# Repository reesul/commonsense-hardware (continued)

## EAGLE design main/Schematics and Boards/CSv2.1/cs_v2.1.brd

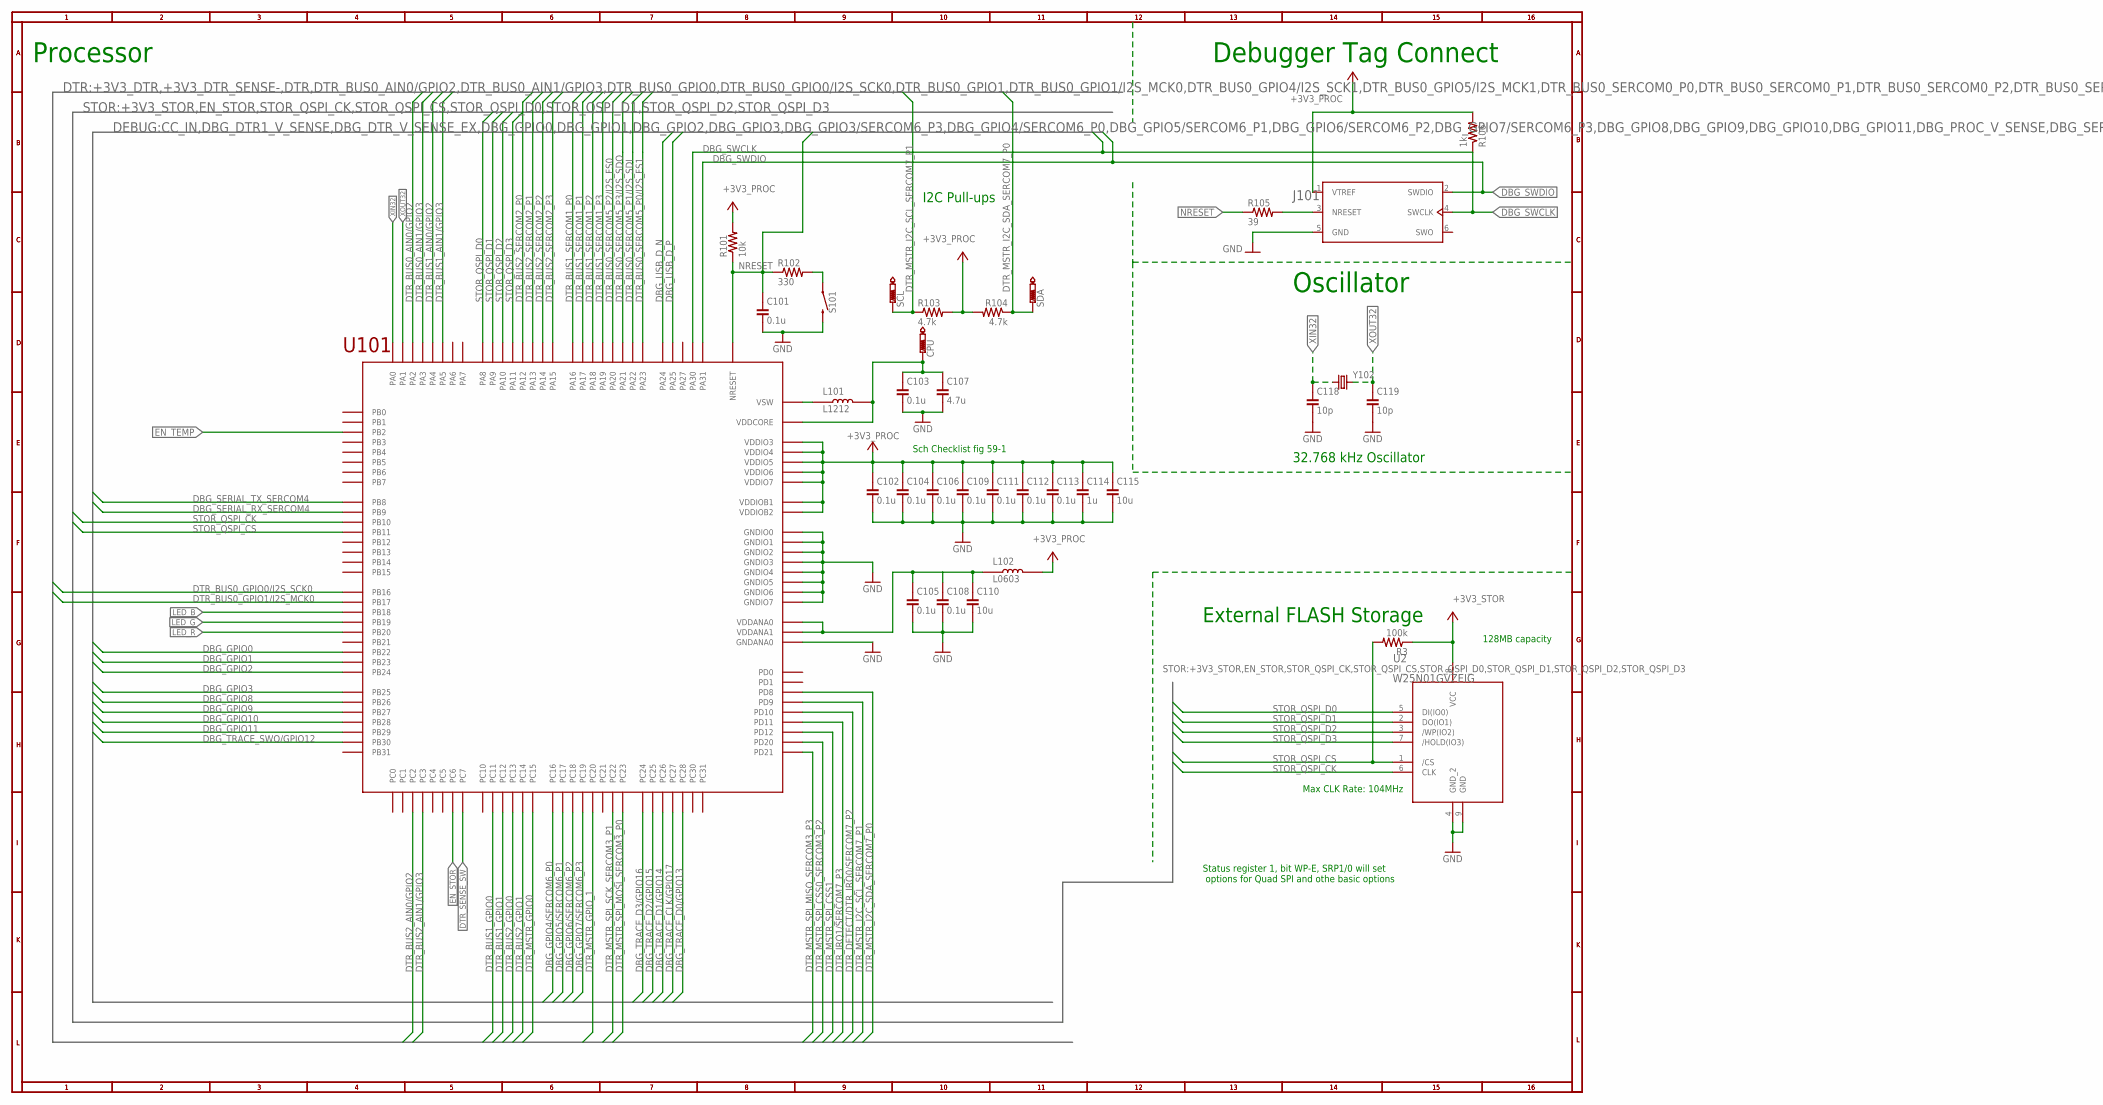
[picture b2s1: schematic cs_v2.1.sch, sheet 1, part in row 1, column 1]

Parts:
C101, C102, C103, C104, C105, C106, C108, C109, C111, C112, C113: 0.1u; C0402; VOLTAGE 10V; PART_NO C0402C104K8RACTU
C107: 4.7u; C0805; VOLTAGE 10V; PART_NO C0805C475K8RACTU
C110, C115: 10u; C0805; VOLTAGE 10V; PART_NO C0805C106M8RACTU
C114: 1u; C0402; VOLTAGE 10V; MPN C0402C105M8PACTU
C118, C119: 10p; C0402; PART_NO C0402C100C8GACTU
CPU: PTR1TP10SQ; TP10SQ
J101: J-JTAG-CORTEX-NEEDLE6-LEGS; 8.06.16_6-PIN_NEEDLE_ADAPTER_LEGS
L101: L1212; PART_NO LQH3NPN100MMEL
L102: L0603; PART_NO BLM18PG471SN1D
R3: 100k; R0402; MPN ERJ-2GEJ104X
R101: 10k; R0402; MPN ERJ-2GEJ103X
R102: 330; R0402; PART_NO ERJ-2GEJ331X
R103, R104: 4.7k; R0402; PART_NO ERJ-2GEJ472X
R105: 39; R0402; PART_NO ERJ-2GEJ390X
R106: 1k; R0402; PART_NO ERJ-2GEJ102X
S101: SW_EVQ-P7L01P_SPST_RA; SW_EVQ-P7L01P
SCL: PTR1TP10SQ; TP10SQ
SDA: PTR1TP10SQ; TP10SQ
U2: W25N01GVZEIG; WSON-8_W15N; MANUFACTURER_PART_NUMBER W25N01GVZEIG TR
U101: ATSAMD51; TFBGA120
Y102: ABS07-32.768KHZ-9-T; XTAL320X150X90

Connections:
+3V3_PROC: C102.1, C104.1, C106.1, C109.1, C111.1, C112.1, C113.1, C114.1, C115.1, J101.1 (VTREF), L102.2, R101.2, R103.2, R104.2, R106.2, U101.VDDIO3, U101.VDDIO4, U101.VDDIO5, U101.VDDIO6, U101.VDDIO7, U101.VDDIOB1, U101.VDDIOB2; also elsewhere on the board
+3V3_STOR: R3.1, U2.8 (VCC); also elsewhere on the board
DBG_GPIO0: U101.PB22; also elsewhere on the board
DBG_GPIO1: U101.PB23; also elsewhere on the board
DBG_GPIO2: U101.PB24; also elsewhere on the board
DBG_GPIO3: U101.PB25; also elsewhere on the board
DBG_GPIO4/SERCOM6_P0: U101.PC16; also elsewhere on the board
DBG_GPIO5/SERCOM6_P1: U101.PC17; also elsewhere on the board
DBG_GPIO6/SERCOM6_P2: U101.PC18; also elsewhere on the board
DBG_GPIO7/SERCOM6_P3: U101.PC19; also elsewhere on the board
DBG_GPIO8: U101.PB26; also elsewhere on the board
DBG_GPIO9: U101.PB27; also elsewhere on the board
DBG_GPIO10: U101.PB28; also elsewhere on the board
DBG_GPIO11: U101.PB29; also elsewhere on the board
DBG_SERIAL_RX_SERCOM4: U101.PB09 (PB9); also elsewhere on the board
DBG_SERIAL_TX_SERCOM4: U101.PB08 (PB8); also elsewhere on the board
DBG_SWCLK: J101.4 (SWCLK), R106.1, U101.PA30; also elsewhere on the board
DBG_SWDIO: J101.2 (SWDIO), U101.PA31; also elsewhere on the board
DBG_TRACE_CLK/GPIO17: U101.PC27; also elsewhere on the board
DBG_TRACE_D0/GPIO13: U101.PC28; also elsewhere on the board
DBG_TRACE_D1/GPIO14: U101.PC26; also elsewhere on the board
DBG_TRACE_D2/GPIO15: U101.PC25; also elsewhere on the board
DBG_TRACE_D3/GPIO16: U101.PC24; also elsewhere on the board
DBG_TRACE_SWO/GPIO12: U101.PB30; also elsewhere on the board
DBG_USB_D_N: U101.PA24; also elsewhere on the board
DBG_USB_D_P: U101.PA25; also elsewhere on the board
DTR_BUS0_AIN0/GPIO2: U101.PA02 (PA2); also elsewhere on the board
DTR_BUS0_AIN1/GPIO3: U101.PA03 (PA3); also elsewhere on the board
DTR_BUS0_GPIO0/I2S_SCK0: U101.PB16; also elsewhere on the board
DTR_BUS0_GPIO1/I2S_MCK0: U101.PB17; also elsewhere on the board
DTR_BUS0_SERCOM5_P0/I2S_FS1: U101.PA23; also elsewhere on the board
DTR_BUS0_SERCOM5_P1/I2S_SDI: U101.PA22; also elsewhere on the board
DTR_BUS0_SERCOM5_P2/I2S_FS0: U101.PA20; also elsewhere on the board
DTR_BUS0_SERCOM5_P3/I2S_SDO: U101.PA21; also elsewhere on the board
DTR_BUS1_AIN0/GPIO2: U101.PA04 (PA4); also elsewhere on the board
DTR_BUS1_AIN1/GPIO3: U101.PA05 (PA5); also elsewhere on the board
DTR_BUS1_GPIO0: U101.PC11; also elsewhere on the board
DTR_BUS1_GPIO1: U101.PC12; also elsewhere on the board
DTR_BUS1_SERCOM1_P0: U101.PA16; also elsewhere on the board
DTR_BUS1_SERCOM1_P1: U101.PA17; also elsewhere on the board
DTR_BUS1_SERCOM1_P2: U101.PA18; also elsewhere on the board
DTR_BUS1_SERCOM1_P3: U101.PA19; also elsewhere on the board
DTR_BUS2_AIN0/GPIO2: U101.PC02 (PC2); also elsewhere on the board
DTR_BUS2_AIN1/GPIO3: U101.PC03 (PC3); also elsewhere on the board
DTR_BUS2_GPIO0: U101.PC13; also elsewhere on the board
DTR_BUS2_GPIO1: U101.PC14; also elsewhere on the board
DTR_BUS2_SERCOM2_P0: U101.PA12; also elsewhere on the board
DTR_BUS2_SERCOM2_P1: U101.PA13; also elsewhere on the board
DTR_BUS2_SERCOM2_P2: U101.PA14; also elsewhere on the board
DTR_BUS2_SERCOM2_P3: U101.PA15; also elsewhere on the board
DTR_DETECT/DTR_IRQ0/SERCOM7_P2: U101.PD10; also elsewhere on the board
DTR_IRQ1/SERCOM7_P3: U101.PD11; also elsewhere on the board
DTR_MSTR_GPIO0: U101.PC15; also elsewhere on the board
DTR_MSTR_GPIO_1: U101.PC20
DTR_MSTR_I2C_SCL_SERCOM7_P1: R103.1, SCL.TP, U101.PD09 (PD9); also elsewhere on the board
DTR_MSTR_I2C_SDA_SERCOM7_P0: R104.1, SDA.TP, U101.PD08 (PD8); also elsewhere on the board
DTR_MSTR_SPI_CSS0_SERCOM3_P2: U101.PD20; also elsewhere on the board
DTR_MSTR_SPI_CSS1: U101.PD12; also elsewhere on the board
DTR_MSTR_SPI_MISO_SERCOM3_P3: U101.PD21; also elsewhere on the board
DTR_MSTR_SPI_MOSI_SERCOM3_P0: U101.PC23; also elsewhere on the board
DTR_MSTR_SPI_SCK_SERCOM3_P1: U101.PC22; also elsewhere on the board
DTR_SENSE_SW: U101.PC07 (PC7); also elsewhere on the board
EN_STOR: U101.PC06 (PC6); also elsewhere on the board
EN_TEMP: U101.PB02 (PB2); also elsewhere on the board
GND: C101.2, C102.2, C103.2, C104.2, C105.2, C106.2, C107.2, C108.2, C109.2, C110.2, C111.2, C112.2, C113.2, C114.2, C115.2, C118.2, C119.2, J101.5 (GND), S101.2_1 (2), S101.2_2 (2), U2.4 (GND_2), U2.9 (GND), U101.GNDANA0, U101.GNDIO0, U101.GNDIO1, U101.GNDIO2, U101.GNDIO3, U101.GNDIO4, U101.GNDIO5, U101.GNDIO6, U101.GNDIO7; also elsewhere on the board
JTAG_NRESET: J101.3 (NRESET), R105.2
LED_B: U101.PB18; also elsewhere on the board
LED_G: U101.PB19; also elsewhere on the board
LED_R: U101.PB20; also elsewhere on the board
unnamed: R102.2, S101.1_1 (1), S101.1_2 (1)
NRESET: C101.1, R101.1, R102.1, R105.1, U101.NRESET; also elsewhere on the board
STOR_QSPI_CK: U2.6 (CLK), U101.PB10
STOR_QSPI_CS: R3.2, U2.1 (/CS), U101.PB11
STOR_QSPI_D0: U2.5 (DI(IO0)), U101.PA08 (PA8)
STOR_QSPI_D1: U2.2 (DO(IO1)), U101.PA09 (PA9)
STOR_QSPI_D2: U2.3 (/WP(IO2)), U101.PA10
STOR_QSPI_D3: U2.7 (/HOLD(IO3)), U101.PA11
VDDANA: C105.1, C108.1, C110.1, L102.1, U101.VDDANA0, U101.VDDANA1
VDDCORE: C103.1, C107.1, CPU.TP, L101.P$2 (2), U101.VDDCORE
VSW: L101.P$1 (1), U101.VSW
XIN32: C118.1, U101.PA00 (PA0), Y102.1
XOUT32: C119.1, U101.PA01 (PA1), Y102.2

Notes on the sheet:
Sch Checklist fig 59-1
Oscillator
32.768 kHz Oscillator
Processor
Debugger Tag Connect
I2C Pull-ups
External FLASH Storage
128MB capacity
Max CLK Rate: 104MHz
Status register 1, bit WP-E, SRP1/0 will set options for Quad SPI and othe basic options

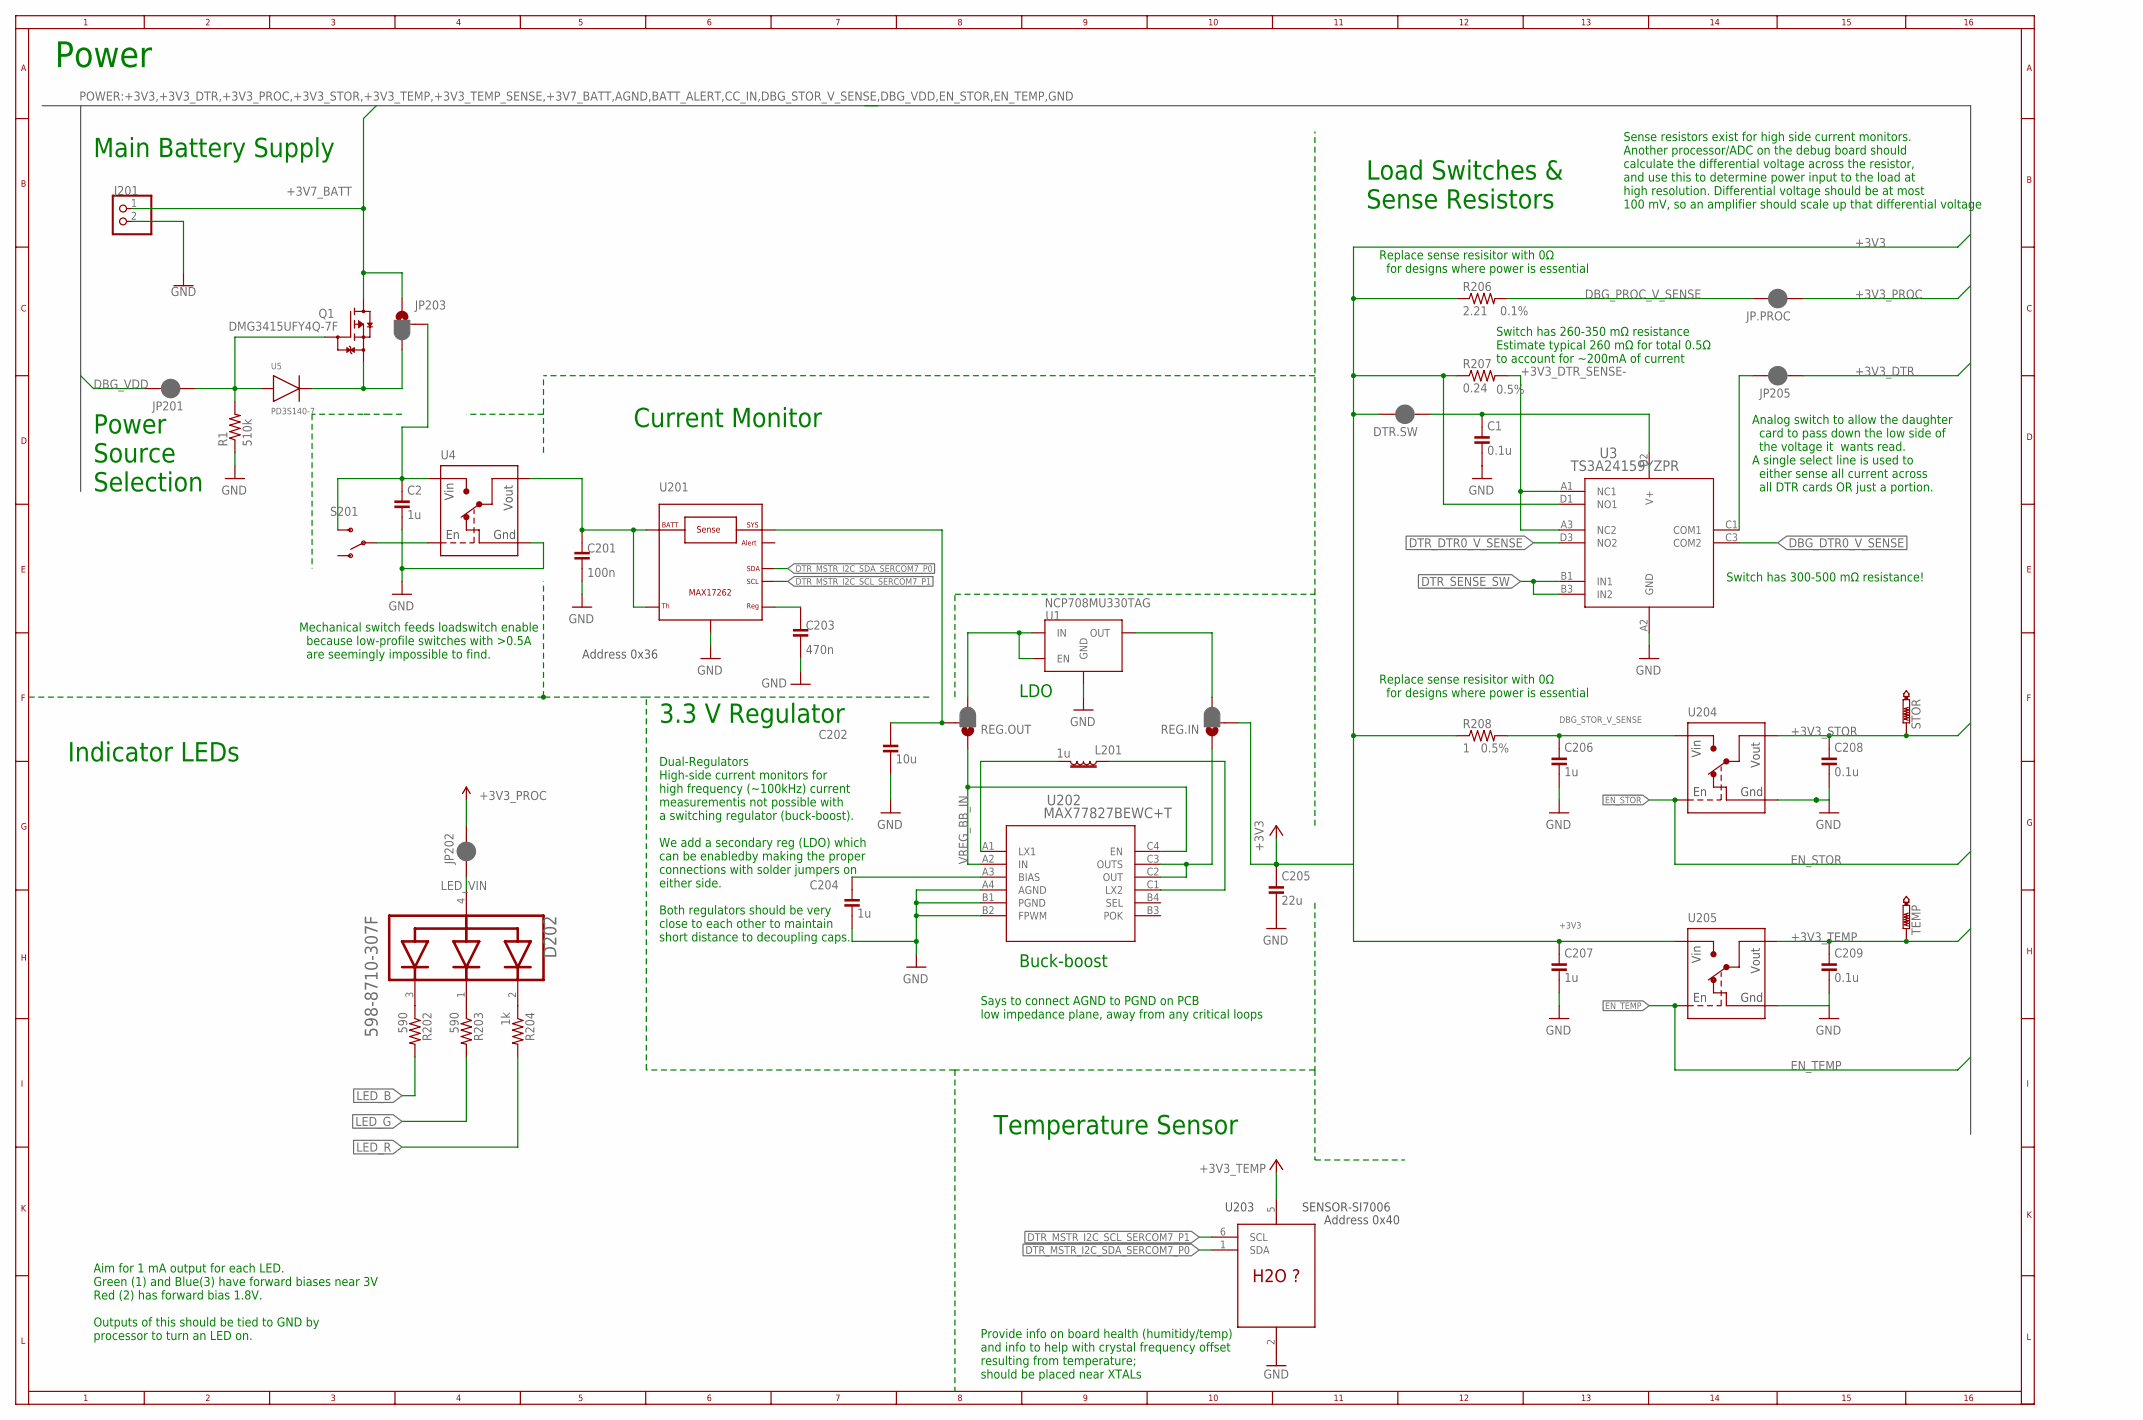
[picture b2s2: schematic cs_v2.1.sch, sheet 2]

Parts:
C1, C208, C209: 0.1u; C0402; VOLTAGE 10V; PART_NO C0402C104K8RACTU
C2, C206, C207: 1u; C0402; VOLTAGE 10V; PART_NO C0402C105M8PACTU
C201: 100n; C0402; PART_NO CC0402KRX5R5BB104
C202: 10u; C0603; VOLTAGE 10V; PART_NO C0603C106M8PAC7867
C203: 470n; C0402; PART_NO CC0402KRX5R5BB474
C204: 1u; C0402; VOLTAGE 10V; MPN C0402C105M8PACTU
C205: 22u; C0805; VOLTAGE 10V; PART_NO C0805C226M8PAC7800
D202: DIALIGHT_RGBLED_598-8710-307FDIALIGHT_598-8710-30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; DIALIGHT_0606_598-8710-307F_0; PART_NO 598-8710-307F
DTR.SW: JUMPER-SMT_2_NC_PASTE_NO-SILK; SMT-JUMPER_2_NC_PASTE_NO-SILK
J201: J-JST2-SMT-RA; JST-PH-2-SMT-RA; PART_NO S2B-PH-SM4-TB(LF)(SN)
JP201, JP202, JP205, JP.PROC: JUMPER-SMT_2_NC_PASTE_NO-SILK; SMT-JUMPER_2_NC_PASTE_NO-SILK
JP203: JUMPER-SMT_3_1-NC_PASTE_NO-SILK; SMT-JUMPER_3_1-NC_PASTE_NO-SILK
L201: 1u; XAL40; PART_NO XAL4020-102MEC
Q1: DMG3415UFY4Q-7F; X2-DFN2015-3; MPN DMG3415UFY4Q-7
R1: 510k; R0402; MPN ERJ-2GEJ514X
R202, R203: 590; R0402; PART_NO ERJ-2RKF5900X
R204: 1k; R0402; PART_NO ERA-2AED102X
R206: 2.21; R0603; MPN RNCF0603BKC2R21
R207: 0.24; R0402; MPN KDV06DR240ET
R208: 1; R0603; MPN KDV06DR510ET
REG.IN, REG.OUT: JUMPER-SMT_3_1-NC_PASTE_NO-SILK; SMT-JUMPER_3_1-NC_PASTE_NO-SILK
S201: SLIDESWITCH-SPDT-SMD-RIGHT-ANGLE; SWITCH_SPST_SMD_A; PART_NO CUS-12TB
STOR: PTR1TP10SQ; TP10SQ
TEMP: PTR1TP10SQ; TP10SQ
U1: NCP708MU330TAG; UDFN6_NCP708]
U3: TS3A24159YZPR; DSBGA10; MPN TS3A24159YZPR
U4, U204, U205: LOADSWITCH-MIC94164; WLCSP6_2X3; PART_NO MIC94164YCS-TR
U5: PD3S140-7; POWERDI323
U201: COULOMB-MAX17262; BGA9N40P3X3_144X146X69N; PART_NO MAX17262REWL+T
U202: MAX77827BEWC+T; 12-WLP; PART_NO MAX77827BEWC+T
U203: SENSOR-SI7006; DFN-06; PART_NO SI7021-A20-GM1R

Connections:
+3V3: C205.1, C207.1, DTR.SW.2, R206.1, R207.1, R208.1, REG.IN.2, U3.D1 (NO1), U205.A2 (VIN), U205.B2 (VIN); also elsewhere on the board
+3V3_DTR: JP205.1; also elsewhere on the board
+3V3_DTR.SW: JP205.2, U3.C1 (COM1)
+3V3_DTR_SENSE-: R207.2, U3.A1 (NC1), U3.A3 (NC2)
+3V3_PROC: JP202.2, JP.PROC.1; also elsewhere on the board
+3V3_STOR: C208.1, STOR.TP, U204.A1 (VOUT), U204.B1 (VOUT); also elsewhere on the board
+3V3_TEMP: C209.1, TEMP.TP, U203.5 (V), U205.A1 (VOUT), U205.B1 (VOUT)
+3V7_BATT: J201.1 (2), JP203.1, Q1.3-1 (D), Q1.3-2 (D); also elsewhere on the board
BB_LX1: L201.2, U202.A1 (LX1)
BB_LX2: L201.1, U202.C1 (LX2)
BB_REG_OUT: REG.IN.1, U202.C2 (OUT), U202.C3 (OUTS)
CC_IN: C201.1, U4.A1 (VOUT), U4.B1 (VOUT), U201.A1 (TH), U201.A2 (BATT)
DBG_DTR0_V_SENSE: U3.C3 (COM2); also elsewhere on the board
DBG_PROC_V_SENSE: JP.PROC.2, R206.2; also elsewhere on the board
DBG_STOR_V_SENSE: C206.1, R208.2, U204.A2 (VIN), U204.B2 (VIN); also elsewhere on the board
DBG_VDD: JP201.2; also elsewhere on the board
DTR_DTR0_V_SENSE: U3.D3 (NO2); also elsewhere on the board
DTR_MSTR_I2C_SCL_SERCOM7_P1: U201.B1 (SCL), U203.6 (SCL); also elsewhere on the board
DTR_MSTR_I2C_SDA_SERCOM7_P0: U201.C1 (SDA), U203.1 (SDA); also elsewhere on the board
DTR_SENSE_SW: U3.B1 (IN1), U3.B3 (IN2); also elsewhere on the board
EN_STOR: U204.C2 (ENABLE); also elsewhere on the board
EN_TEMP: U205.C2 (ENABLE); also elsewhere on the board
GND: C1.2, C2.2, C201.2, C202.2, C203.2, C204.2, C205.2, C206.2, C207.2, C208.2, C209.2, J201.2 (1), R1.1, U1.2 (GND), U1.3 (GND), U1.7 (GND), U3.A2 (GND), U4.C1 (GND), U201.C3 (GND), U202.A4 (AGND), U202.B1 (PGND), U202.B2 (FPWM), U203.2 (GND), U204.C1 (GND), U205.C1 (GND); also elsewhere on the board
LDO_REG_OUT: REG.IN.3, U1.4 (OUT), U1.5 (OUT)
LED_B: R202.2; also elsewhere on the board
LED_G: R203.2; also elsewhere on the board
LED_R: R204.2; also elsewhere on the board
LED_VIN: D202.4 (COMMON_ANODE), JP202.1
unnamed: JP203.3, Q1.2 (S), U5.2 (N)
unnamed: D202.3 (BLUE_CATHODE), R202.1
unnamed: D202.1 (GREEN_CATHODE), R203.1
unnamed: C203.1, U201.C2 (REG)
unnamed: D202.2 (RED_CATHODE), R204.1
unnamed: C1.1, DTR.SW.1, U3.D2 (V+)
REG_LDO_IN: REG.OUT.3, U1.1 (EN), U1.6 (IN)
V.SRC: C2.1, JP203.2, S201.3 (S), U4.A2 (VIN), U4.B2 (VIN)
V.SRC.EN: S201.2, U4.C2 (ENABLE)
VREG_BB_IN: REG.OUT.1, U202.A2 (IN), U202.C4 (EN)
VREG_BIAS: C204.1, U202.A3 (BIAS)
VREG_IN: C202.1, REG.OUT.2, U201.B3 (SYS)
V_SEL_IN_B: JP201.1, Q1.1 (G), R1.2, U5.1

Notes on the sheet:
Sense resistors exist for high side current monitors. Another processor/ADC on the debug board should calculate the differential voltage across the resistor, and use this to determine power input to the load at high resolution. Differential voltage should be at most 100 mV, so an amplifier should s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
Power
3.3 V Regulator
Power Source Selection
Main Battery Supply
Load Switches & Sense Resistors
Buck-boost
Aim for 1 mA output for each LED. Green (1) and Blue(3) have forward biases near 3V Red (2) has forward bias 1.8V. Outputs of this should be tied to GND by processor to turn an LED on.
Indicator LEDs
Temperature Sensor
Says to connect AGND to PGND on PCB low impedance plane, away from any critical loops
Provide info on board health (humitidy/temp) and info to help with crystal frequency offset resulting from temperature; should be placed near XTALs
Current Monitor
LDO
Dual-Regulators High-side current monitors for high frequency (~100kHz) current measurementis not possible with a switching regulator (buck-boost). We add a secondary reg (LDO) which can be enabledby making the proper connections with solder jumpers on either side. Both regulators should be very cl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
Analog switch to allow the daughter card to pass down the low side of the voltage it wants read. A single select line is used to either sense all current across all DTR cards OR just a portion.
Mechanical switch feeds loadswitch enable because low-profile switches with >0.5A are seemingly impossible to find.
Replace sense resisitor with 0Ω for designs where power is essential
Switch has 300-500 mΩ resistance!
Switch has 260-350 mΩ resistance Estimate typical 260 mΩ for total 0.5Ω to account for ~200mA of current
Address 0x40
Address 0x36

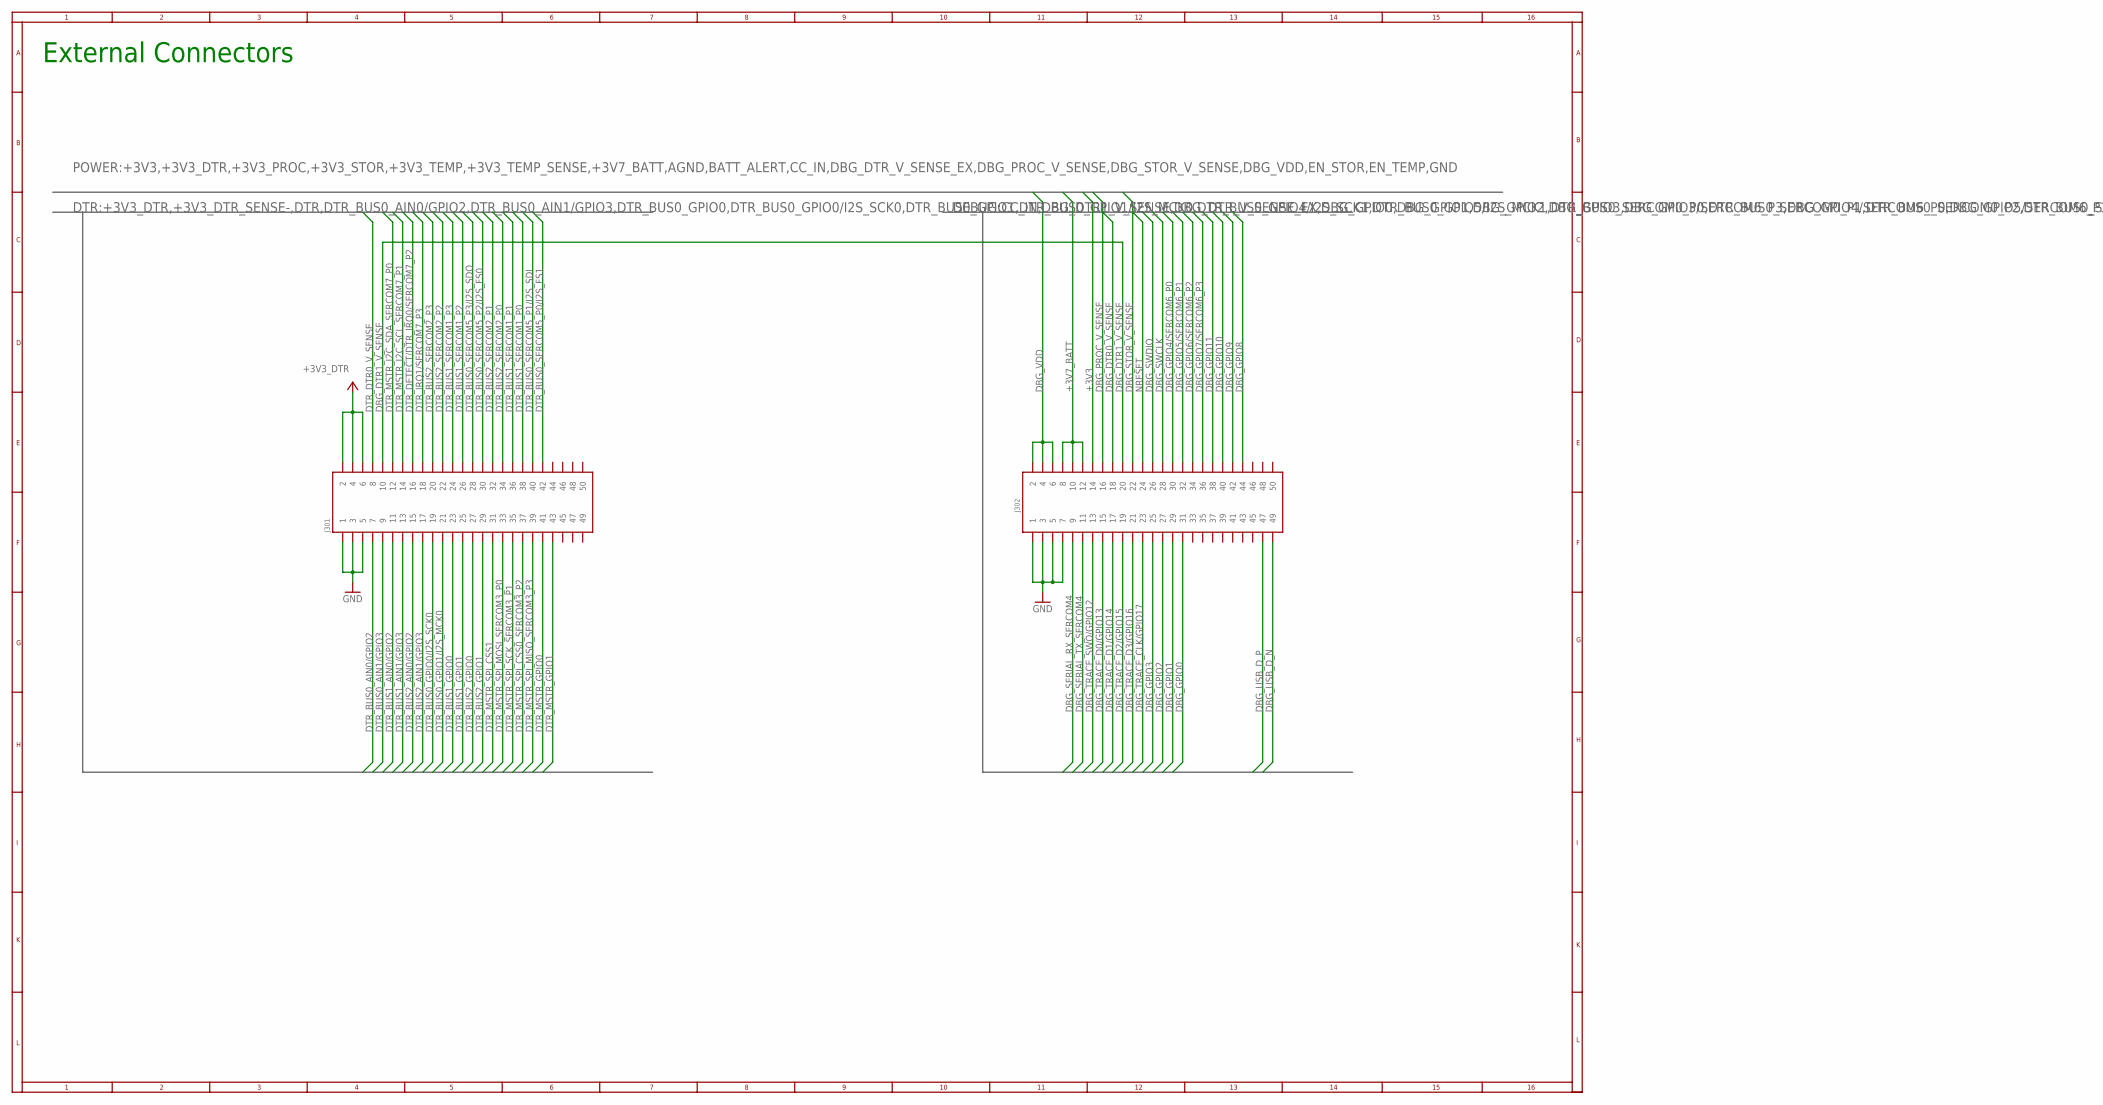
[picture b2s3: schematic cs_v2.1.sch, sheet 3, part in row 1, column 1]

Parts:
J301, J302: HIROSE-DF40_50-PIN_CONNECTORS-RECEPTACLE; HRS_DF40HC(4.0)-50DS-0.4V(51); MPN DF40HC(4.0)-50DS-0.4V(51)

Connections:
+3V3: J302.14; also elsewhere on the board
+3V3_DTR: J301.2, J301.4, J301.6; also elsewhere on the board
+3V7_BATT: J302.8, J302.10, J302.12; also elsewhere on the board
DBG_DTR0_V_SENSE: J302.18; also elsewhere on the board
DBG_DTR1_V_SENSE: J301.10, J302.20
DBG_GPIO0: J302.31; also elsewhere on the board
DBG_GPIO1: J302.29; also elsewhere on the board
DBG_GPIO2: J302.27; also elsewhere on the board
DBG_GPIO3: J302.25; also elsewhere on the board
DBG_GPIO4/SERCOM6_P0: J302.30; also elsewhere on the board
DBG_GPIO5/SERCOM6_P1: J302.32; also elsewhere on the board
DBG_GPIO6/SERCOM6_P2: J302.34; also elsewhere on the board
DBG_GPIO7/SERCOM6_P3: J302.36; also elsewhere on the board
DBG_GPIO8: J302.44; also elsewhere on the board
DBG_GPIO9: J302.42; also elsewhere on the board
DBG_GPIO10: J302.40; also elsewhere on the board
DBG_GPIO11: J302.38; also elsewhere on the board
DBG_PROC_V_SENSE: J302.16; also elsewhere on the board
DBG_SERIAL_RX_SERCOM4: J302.9; also elsewhere on the board
DBG_SERIAL_TX_SERCOM4: J302.11; also elsewhere on the board
DBG_STOR_V_SENSE: J302.22; also elsewhere on the board
DBG_SWCLK: J302.28; also elsewhere on the board
DBG_SWDIO: J302.26; also elsewhere on the board
DBG_TRACE_CLK/GPIO17: J302.23; also elsewhere on the board
DBG_TRACE_D0/GPIO13: J302.15; also elsewhere on the board
DBG_TRACE_D1/GPIO14: J302.17; also elsewhere on the board
DBG_TRACE_D2/GPIO15: J302.19; also elsewhere on the board
DBG_TRACE_D3/GPIO16: J302.21; also elsewhere on the board
DBG_TRACE_SWO/GPIO12: J302.13; also elsewhere on the board
DBG_USB_D_N: J302.49; also elsewhere on the board
DBG_USB_D_P: J302.47; also elsewhere on the board
DBG_VDD: J302.2, J302.4, J302.6; also elsewhere on the board
DTR_BUS0_AIN0/GPIO2: J301.7; also elsewhere on the board
DTR_BUS0_AIN1/GPIO3: J301.9; also elsewhere on the board
DTR_BUS0_GPIO0/I2S_SCK0: J301.19; also elsewhere on the board
DTR_BUS0_GPIO1/I2S_MCK0: J301.21; also elsewhere on the board
DTR_BUS0_SERCOM5_P0/I2S_FS1: J301.42; also elsewhere on the board
DTR_BUS0_SERCOM5_P1/I2S_SDI: J301.40; also elsewhere on the board
DTR_BUS0_SERCOM5_P2/I2S_FS0: J301.30; also elsewhere on the board
DTR_BUS0_SERCOM5_P3/I2S_SDO: J301.28; also elsewhere on the board
DTR_BUS1_AIN0/GPIO2: J301.11; also elsewhere on the board
DTR_BUS1_AIN1/GPIO3: J301.13; also elsewhere on the board
DTR_BUS1_GPIO0: J301.23; also elsewhere on the board
DTR_BUS1_GPIO1: J301.25; also elsewhere on the board
DTR_BUS1_SERCOM1_P0: J301.38; also elsewhere on the board
DTR_BUS1_SERCOM1_P1: J301.36; also elsewhere on the board
DTR_BUS1_SERCOM1_P2: J301.26; also elsewhere on the board
DTR_BUS1_SERCOM1_P3: J301.24; also elsewhere on the board
DTR_BUS2_AIN0/GPIO2: J301.15; also elsewhere on the board
DTR_BUS2_AIN1/GPIO3: J301.17; also elsewhere on the board
DTR_BUS2_GPIO0: J301.27; also elsewhere on the board
DTR_BUS2_GPIO1: J301.29; also elsewhere on the board
DTR_BUS2_SERCOM2_P0: J301.34; also elsewhere on the board
DTR_BUS2_SERCOM2_P1: J301.32; also elsewhere on the board
DTR_BUS2_SERCOM2_P2: J301.22; also elsewhere on the board
DTR_BUS2_SERCOM2_P3: J301.20; also elsewhere on the board
DTR_DETECT/DTR_IRQ0/SERCOM7_P2: J301.16; also elsewhere on the board
DTR_DTR0_V_SENSE: J301.8; also elsewhere on the board
DTR_IRQ1/SERCOM7_P3: J301.18; also elsewhere on the board
DTR_MSTR_GPIO0: J301.41; also elsewhere on the board
DTR_MSTR_GPIO1: J301.43
DTR_MSTR_I2C_SCL_SERCOM7_P1: J301.14; also elsewhere on the board
DTR_MSTR_I2C_SDA_SERCOM7_P0: J301.12; also elsewhere on the board
DTR_MSTR_SPI_CSS0_SERCOM3_P2: J301.37; also elsewhere on the board
DTR_MSTR_SPI_CSS1: J301.31; also elsewhere on the board
DTR_MSTR_SPI_MISO_SERCOM3_P3: J301.39; also elsewhere on the board
DTR_MSTR_SPI_MOSI_SERCOM3_P0: J301.33; also elsewhere on the board
DTR_MSTR_SPI_SCK_SERCOM3_P1: J301.35; also elsewhere on the board
GND: J301.1, J301.3, J301.5, J302.1, J302.3, J302.5, J302.7; also elsewhere on the board
NRESET: J302.24; also elsewhere on the board

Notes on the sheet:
External Connectors

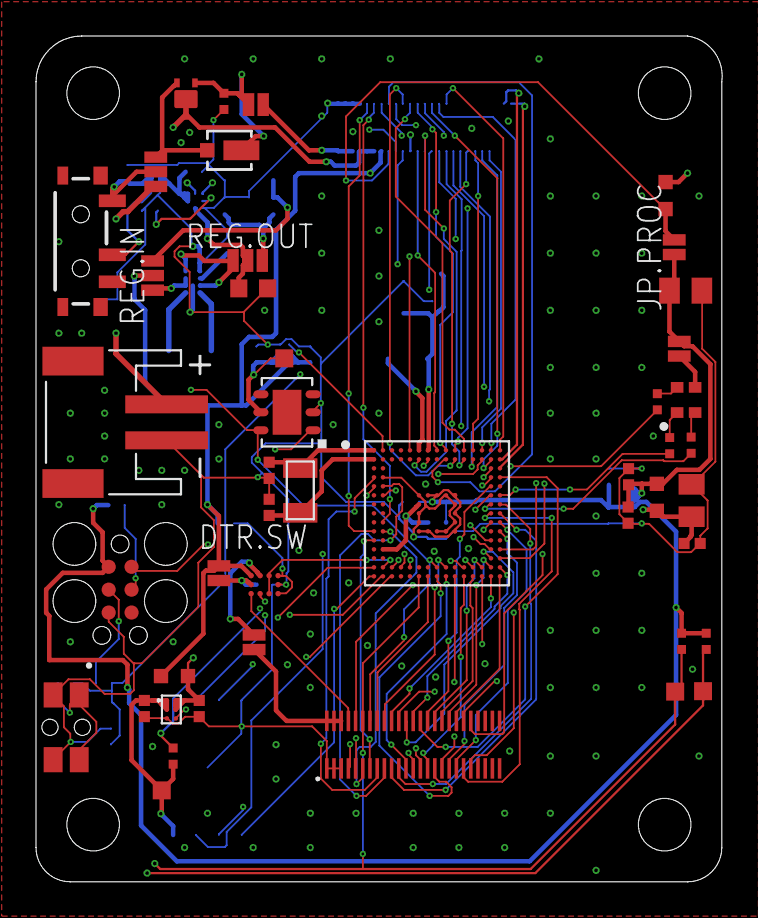
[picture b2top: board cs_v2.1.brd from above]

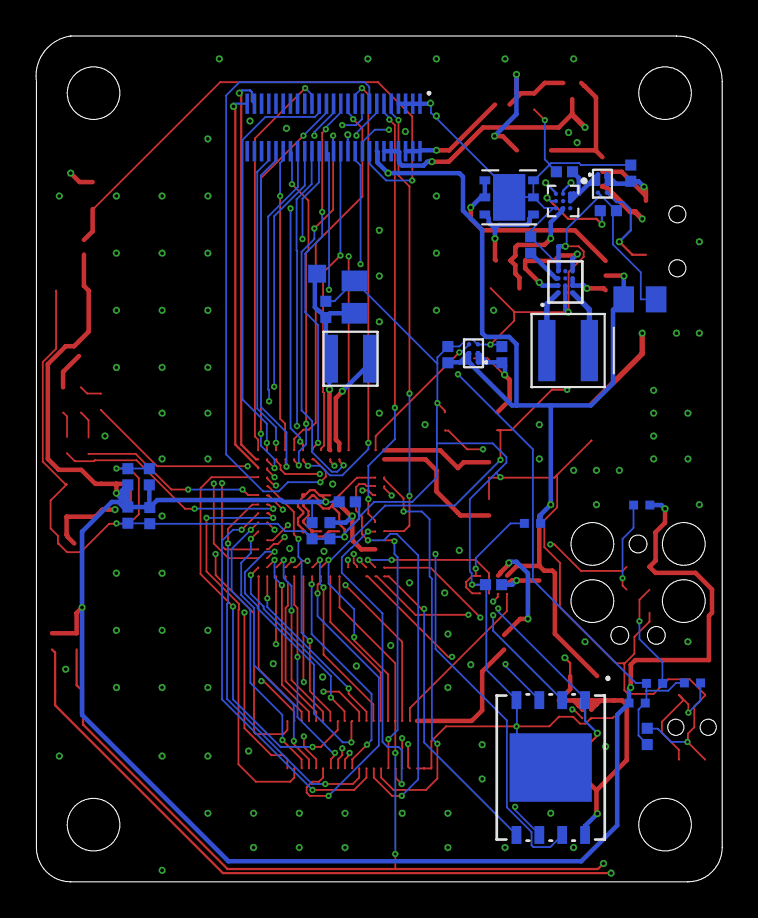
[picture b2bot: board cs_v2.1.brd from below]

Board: 4 copper layers, 38.1 x 47.0 mm, 78 parts (33 on the bottom side), 112 nets.
